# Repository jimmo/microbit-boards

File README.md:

# microbit-boards
Adaptors and breakouts for the micro:bit

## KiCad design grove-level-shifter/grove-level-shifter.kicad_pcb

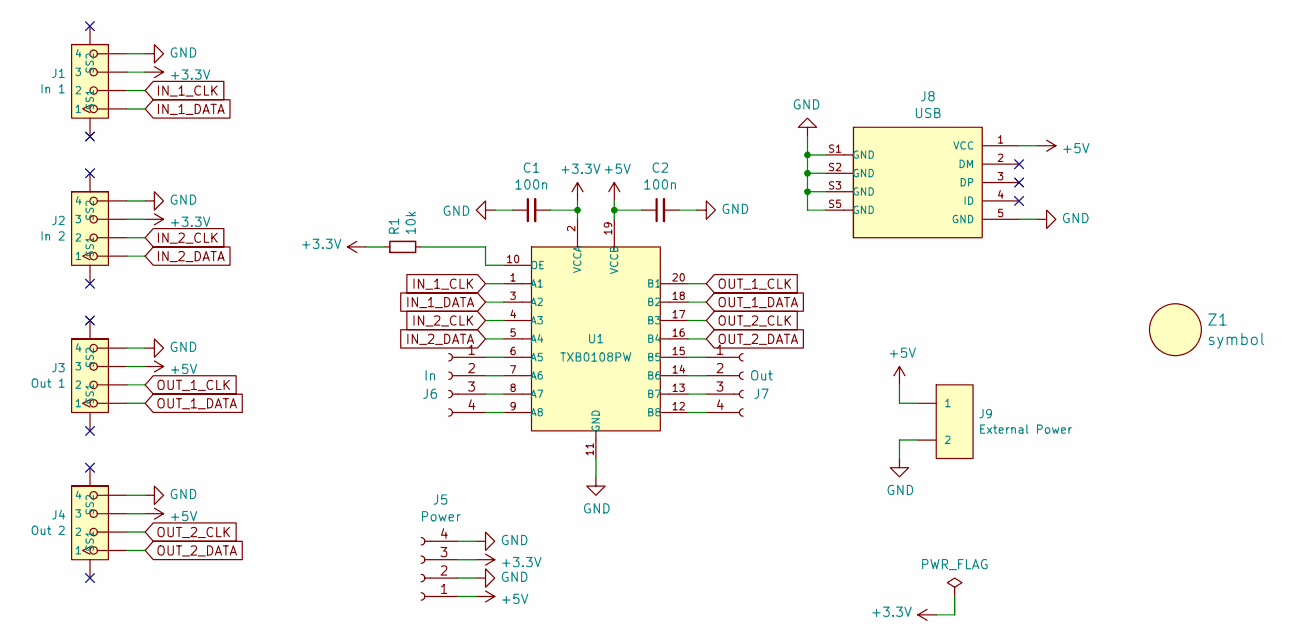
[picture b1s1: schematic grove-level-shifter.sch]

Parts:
C1, C2: 100n; C_0603_HandSoldering
J1: In 1; HW4-SMD-2.0-90D
J2: In 2; HW4-SMD-2.0-90D
J3: Out 1; HW4-SMD-2.0-90D
J4: Out 2; HW4-SMD-2.0-90D
J5: Power; Pin_Header_Straight_1x04_Pitch2.54mm
J6: In; Pin_Header_Straight_1x04_Pitch2.54mm
J7: Out; Pin_Header_Straight_1x04_Pitch2.54mm
J8: USB; MICRO-USB5+6P-SMD-0.65-B
J9: External Power; H2-3.5-7.0X7.0MM
R1: 10k; R_0603_HandSoldering
U1: TXB0108PW; TSSOP20-0.65-6.5X4.4MM; MPN TXB0108PW
Z1: symbol; OSHW-Logo2_7.3x6mm_Copper

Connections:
+3V3: C1.2, J1.3, J2.3, J5.3, R1.1, U1.2 (VCCA)
+5V: C2.1, J3.3, J4.3, J5.1, J8.1 (VCC), J9.1, U1.19 (VCCB)
GND: C1.1, C2.2, J1.4, J2.4, J3.4, J4.4, J5.2, J5.4, J8.5 (GND), J8.S1 (GND), J8.S2 (GND), J8.S3 (GND), J8.S4 (GND), J8.S5 (GND), J8.S6 (GND), J9.2, U1.11 (GND)
IN_1_CLK: J1.2, U1.1 (A1)
IN_1_DATA: J1.1, U1.3 (A2)
IN_2_CLK: J2.2, U1.4 (A3)
IN_2_DATA: J2.1, U1.5 (A4)
unnamed: J6.1, U1.6 (A5)
unnamed: J6.2, U1.7 (A6)
unnamed: J6.3, U1.8 (A7)
unnamed: J6.4, U1.9 (A8)
unnamed: J7.1, U1.15 (B5)
unnamed: J7.2, U1.14 (B6)
unnamed: J7.3, U1.13 (B7)
unnamed: J7.4, U1.12 (B8)
unnamed: R1.2, U1.10 (OE)
OUT_1_CLK: J3.2, U1.20 (B1)
OUT_1_DATA: J3.1, U1.18 (B2)
OUT_2_CLK: J4.2, U1.17 (B3)
OUT_2_DATA: J4.1, U1.16 (B4)

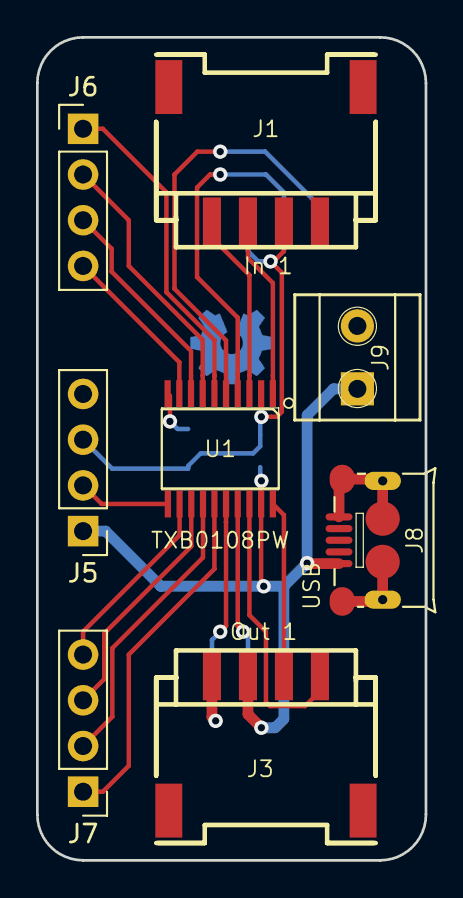
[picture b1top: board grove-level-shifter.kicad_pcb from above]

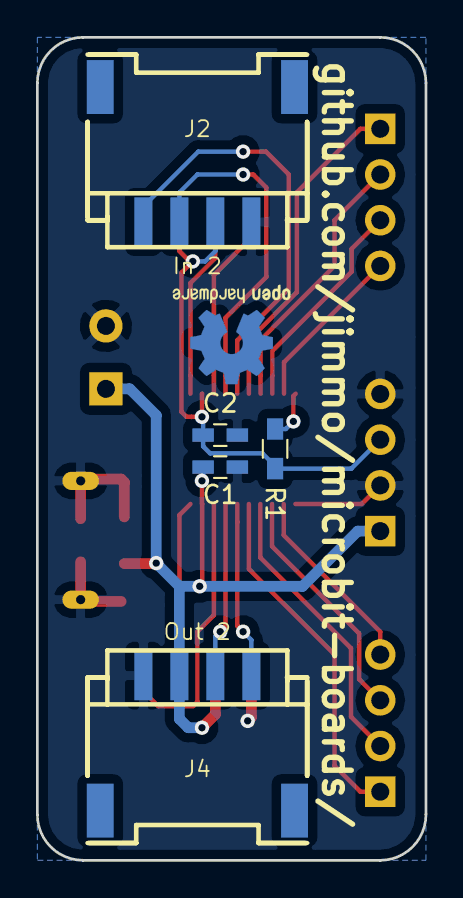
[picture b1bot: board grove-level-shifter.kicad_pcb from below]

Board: 2 copper layers, 21.6 x 45.7 mm, 14 parts (6 on the bottom side), 20 nets.

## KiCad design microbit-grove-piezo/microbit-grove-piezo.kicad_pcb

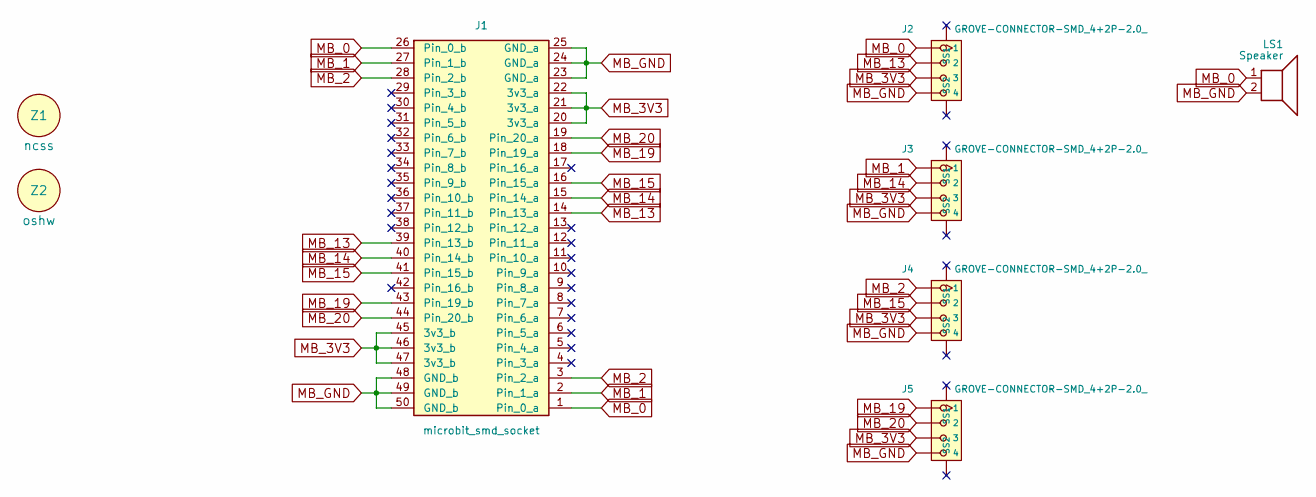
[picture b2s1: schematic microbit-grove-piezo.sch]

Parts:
J1: microbit_smd_socket; smd_socket
J2, J3, J4, J5: GROVE-CONNECTOR-SMD_4+2P-2.0_; HW4-SMD-2.0
LS1: Speaker; PKLCS1212E4001-R1
Z1: ncss; ncss_small
Z2: oshw; OSHW-Logo2_7.3x6mm_Copper_NoText

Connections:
MB_0: J1.1 (Pin_0_a), J1.26 (Pin_0_b), J2.1, LS1.1
MB_1: J1.2 (Pin_1_a), J1.27 (Pin_1_b), J3.1
MB_2: J1.3 (Pin_2_a), J1.28 (Pin_2_b), J4.1
MB_3V3: J1.20 (3v3_a), J1.21 (3v3_a), J1.22 (3v3_a), J1.45 (3v3_b), J1.46 (3v3_b), J1.47 (3v3_b), J2.3, J3.3, J4.3, J5.3
MB_13: J1.14 (Pin_13_a), J1.39 (Pin_13_b), J2.2
MB_14: J1.15 (Pin_14_a), J1.40 (Pin_14_b), J3.2
MB_15: J1.16 (Pin_15_a), J1.41 (Pin_15_b), J4.2
MB_19: J1.18 (Pin_19_a), J1.43 (Pin_19_b), J5.1
MB_20: J1.19 (Pin_20_a), J1.44 (Pin_20_b), J5.2
MB_GND: J1.23 (GND_a), J1.24 (GND_a), J1.25 (GND_a), J1.48 (GND_b), J1.49 (GND_b), J1.50 (GND_b), J2.4, J3.4, J4.4, J5.4, LS1.2

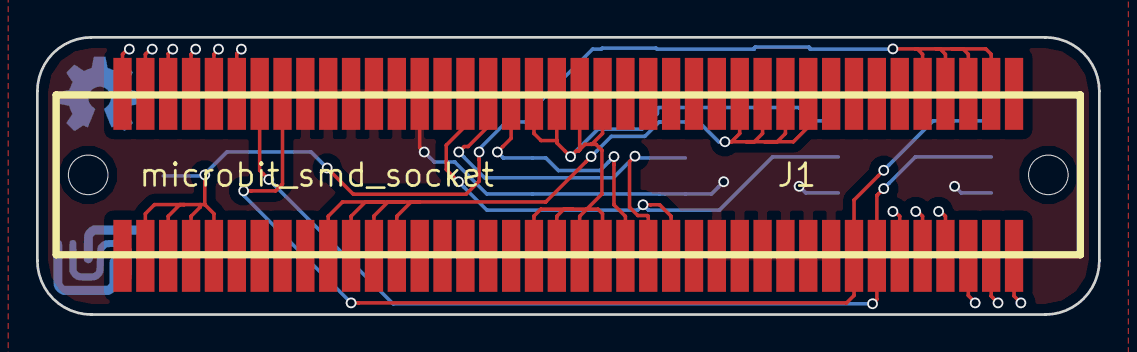
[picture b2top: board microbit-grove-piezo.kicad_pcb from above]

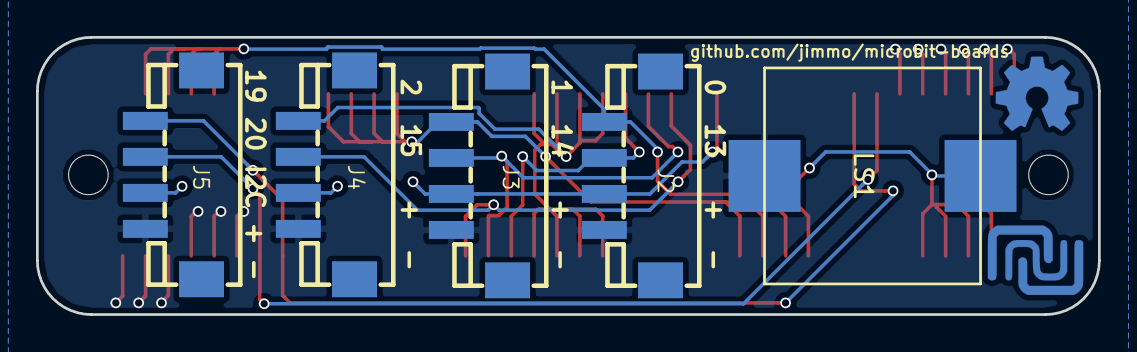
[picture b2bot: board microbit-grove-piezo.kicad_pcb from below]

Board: 2 copper layers, 59.0 x 15.4 mm, 8 parts (7 on the bottom side), 10 nets.

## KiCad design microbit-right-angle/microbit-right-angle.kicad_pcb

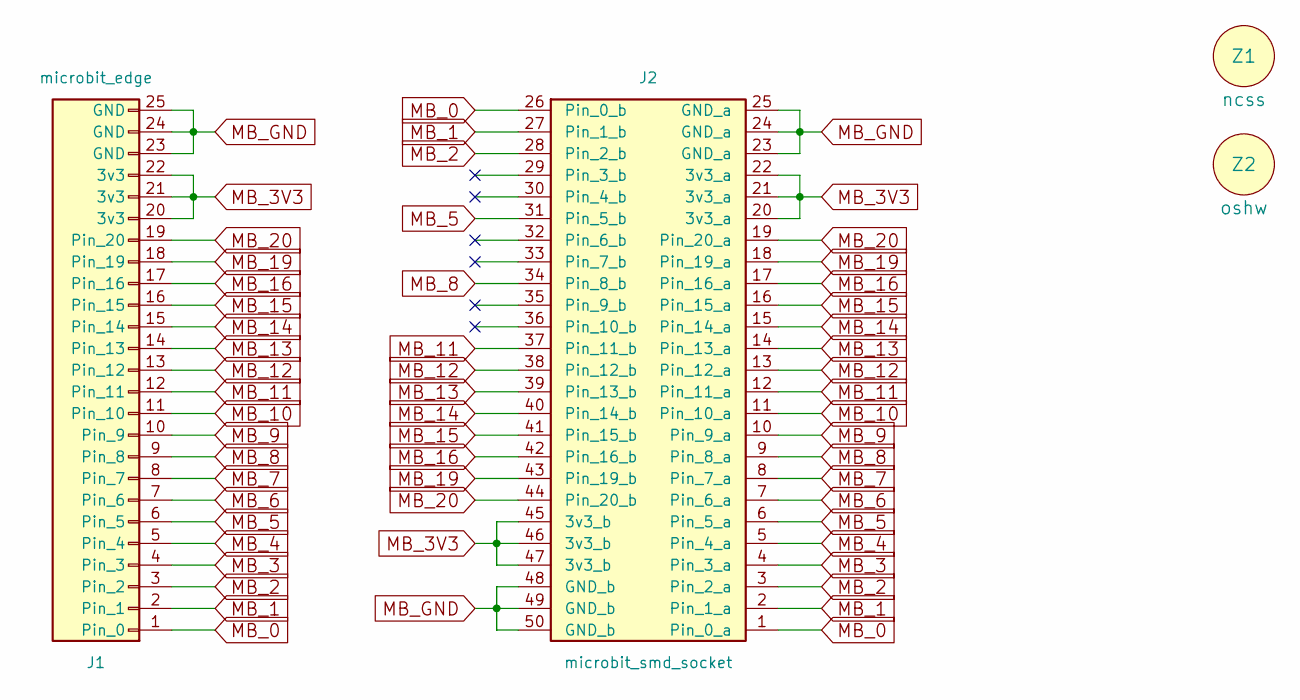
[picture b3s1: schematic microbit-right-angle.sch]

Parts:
J1: microbit_edge
J2: microbit_smd_socket; smd_socket
Z1: ncss
Z2: oshw; OSHW-Logo2_7.3x6mm_Copper

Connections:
MB_0: J1.1 (Pin_0), J2.1 (Pin_0_a), J2.26 (Pin_0_b)
MB_1: J1.2 (Pin_1), J2.2 (Pin_1_a), J2.27 (Pin_1_b)
MB_2: J1.3 (Pin_2), J2.3 (Pin_2_a), J2.28 (Pin_2_b)
MB_3: J1.4 (Pin_3), J2.4 (Pin_3_a)
MB_3V3: J1.20 (3v3), J1.21 (3v3), J1.22 (3v3), J2.20 (3v3_a), J2.21 (3v3_a), J2.22 (3v3_a), J2.45 (3v3_b), J2.46 (3v3_b), J2.47 (3v3_b)
MB_4: J1.5 (Pin_4), J2.5 (Pin_4_a)
MB_5: J1.6 (Pin_5), J2.6 (Pin_5_a), J2.31 (Pin_5_b)
MB_6: J1.7 (Pin_6), J2.7 (Pin_6_a)
MB_7: J1.8 (Pin_7), J2.8 (Pin_7_a)
MB_8: J1.9 (Pin_8), J2.9 (Pin_8_a), J2.34 (Pin_8_b)
MB_9: J1.10 (Pin_9), J2.10 (Pin_9_a)
MB_10: J1.11 (Pin_10), J2.11 (Pin_10_a)
MB_11: J1.12 (Pin_11), J2.12 (Pin_11_a), J2.37 (Pin_11_b)
MB_12: J1.13 (Pin_12), J2.13 (Pin_12_a), J2.38 (Pin_12_b)
MB_13: J1.14 (Pin_13), J2.14 (Pin_13_a), J2.39 (Pin_13_b)
MB_14: J1.15 (Pin_14), J2.15 (Pin_14_a), J2.40 (Pin_14_b)
MB_15: J1.16 (Pin_15), J2.16 (Pin_15_a), J2.41 (Pin_15_b)
MB_16: J1.17 (Pin_16), J2.17 (Pin_16_a), J2.42 (Pin_16_b)
MB_19: J1.18 (Pin_19), J2.18 (Pin_19_a), J2.43 (Pin_19_b)
MB_20: J1.19 (Pin_20), J2.19 (Pin_20_a), J2.44 (Pin_20_b)
MB_GND: J1.23 (GND), J1.24 (GND), J1.25 (GND), J2.23 (GND_a), J2.24 (GND_a), J2.25 (GND_a), J2.48 (GND_b), J2.49 (GND_b), J2.50 (GND_b)

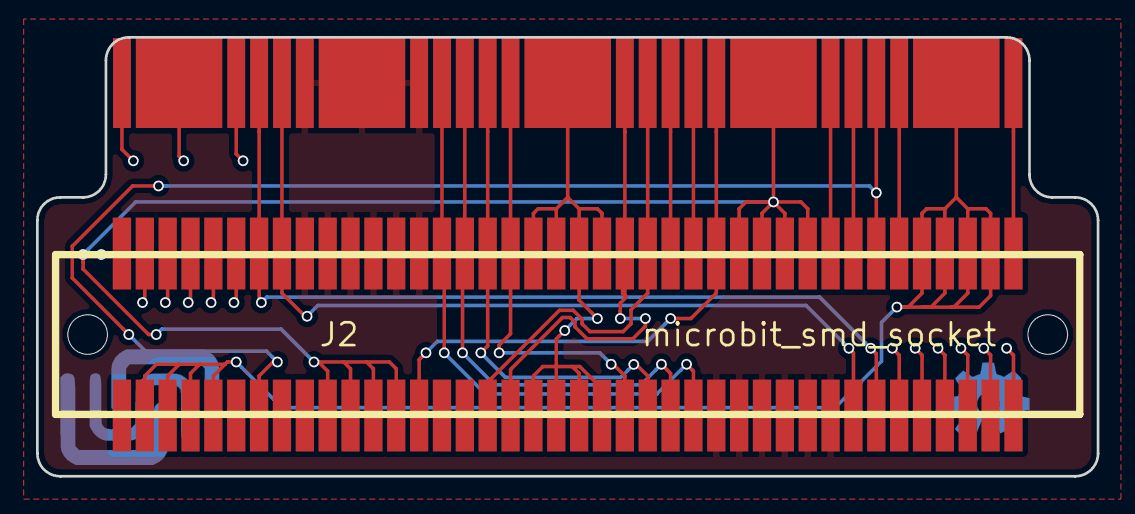
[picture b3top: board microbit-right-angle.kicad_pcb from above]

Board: 2 copper layers, 58.9 x 24.4 mm, 4 parts (2 on the bottom side), 21 nets.

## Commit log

2017-11-29 Simple micro:bit adaptor that adds 4x grove connectors and an optional piezo
2017-11-29 Add right-angle connector for bit:bot
2017-11-29 Add ncss/oshw logos and URL
2017-11-29 Add logos to grove/piezo board
2017-11-30 Make small logos for the grove board.
    Test run gerbers.
2017-11-30 Add seeed gerber scripts
2017-12-03 Update soldermask clearance. Redo big pad connections.
2017-12-03 Use plane fills instead of gnd/vcc traces
2017-12-03 Replace vcc/gnd with pours.
2017-12-03 Fix mask clearance
2017-12-04 Neaten up vias
2017-12-04 Update fills.
2018-11-16 Add more seeed opl parts
2018-11-16 Schematic and unrouted board layout for level shifter
2018-11-16 Routed PCB
2018-11-17 Add gerbers and bom
